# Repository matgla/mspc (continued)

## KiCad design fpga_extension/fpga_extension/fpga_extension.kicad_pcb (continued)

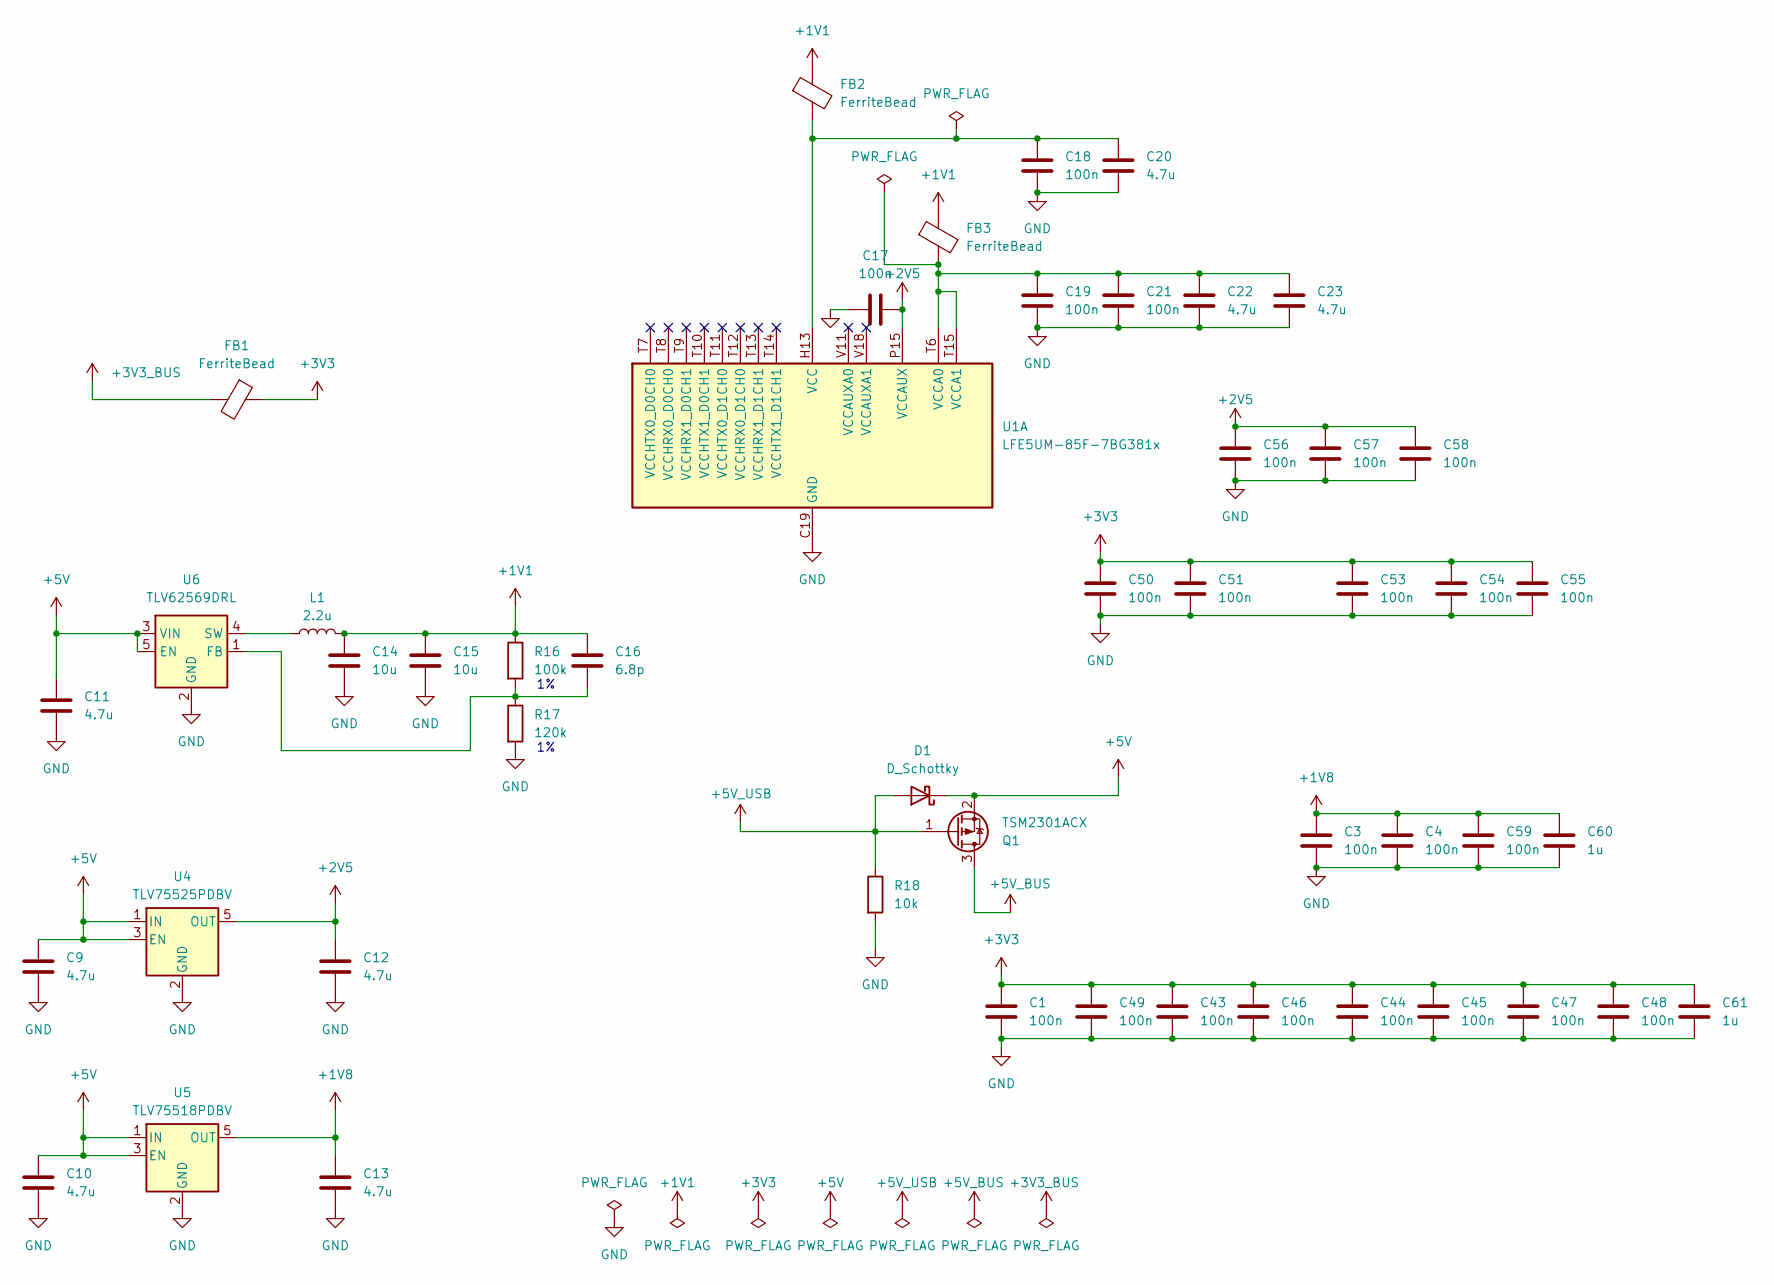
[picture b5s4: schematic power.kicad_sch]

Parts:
C1, C3, C4, C17, C18, C19, C21, C43, C44, C45, C46, C47, C48, C49, C50, C51, C53, C54, C55, C56, C57, C58, C59: 100n; C_0402_1005Metric_Pad0.74x0.62mm_HandSolder
C9, C10, C11, C12, C13, C20, C22, C23: 4.7u; C_0402_1005Metric_Pad0.74x0.62mm_HandSolder
C14, C15: 10u; C_0603_1608Metric_Pad1.08x0.95mm_HandSolder
C16: 6.8p; C_0402_1005Metric_Pad0.74x0.62mm_HandSolder
C60, C61: 1u; C_0402_1005Metric_Pad0.74x0.62mm_HandSolder
D1: D_Schottky; D_SOD-323_HandSoldering
FB1, FB2, FB3: FerriteBead; L_0805_2012Metric_Pad1.05x1.20mm_HandSolder
L1: 2.2u; L_0805_2012Metric_Pad1.15x1.40mm_HandSolder
Q1: TSM2301ACX; SOT-23W_Handsoldering
R16: 100k; R_0402_1005Metric_Pad0.72x0.64mm_HandSolder
R17: 120k; R_0402_1005Metric_Pad0.72x0.64mm_HandSolder
R18: 10k; R_0402_1005Metric_Pad0.72x0.64mm_HandSolder
U1: LFE5UM-85F-7BG381x; Lattice_caBGA-381_17.0x17.0mm_Layout20x20_P0.8mm_Ball0.4mm_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
U4: TLV75525PDBV; SOT-23-5
U5: TLV75518PDBV; SOT-23-5
U6: TLV62569DRL; SOT-563

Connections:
+1V1: C14.1, C15.1, C16.1, FB2.1, FB3.1, L1.2, R16.1
+1V8: C3.1, C4.1, C13.1, C59.1, C60.1, U5.5 (OUT); also elsewhere on the board
+2V5: C12.1, C17.2, C56.1, C57.1, C58.1, U1.F6 (VCCAUX), U1.F15 (VCCAUX), U1.P6 (VCCAUX), U1.P15 (VCCAUX), U4.5 (OUT)
+3V3: C1.1, C43.1, C44.1, C45.1, C46.1, C47.1, C48.1, C49.1, C50.1, C51.1, C53.1, C54.1, C55.1, C61.1, FB1.1; also elsewhere on the board
+3V3_BUS: FB1.2; also elsewhere on the board
+5V: C9.1, C10.1, C11.1, D1.1 (K), Q1.2 (S), U4.1 (IN), U4.3 (EN), U5.1 (IN), U5.3 (EN), U6.3 (VIN), U6.5 (EN)
+5V_BUS: Q1.3 (D); also elsewhere on the board
+5V_USB: D1.2 (A), Q1.1 (G), R18.1; also elsewhere on the board
GND: C1.2, C3.2, C4.2, C9.2, C10.2, C11.2, C12.2, C13.2, C14.2, C15.2, C17.1, C18.2, C19.2, C20.2, C21.2, C22.2, C23.2, C43.2, C44.2, C45.2, C46.2, C47.2, C48.2, C49.2, C50.2, C51.2, C53.2, C54.2, C55.2, C56.2, C57.2, C58.2, C59.2, C60.2, C61.2, R17.2, R18.2, U1.B7 (GND), U1.B14 (GND), U1.C19 (GND), U1.D4 (GND), U1.F7 (GND), U1.F8 (GND), U1.F13 (GND), U1.F14 (GND), U1.G4 (GND), U1.G6 (GND), U1.G7 (GND), U1.G8 (GND), U1.G9 (GND), U1.G10 (GND), U1.G11 (GND), U1.G12 (GND), U1.G13 (GND), U1.G14 (GND), U1.G15 (GND), U1.G17 (GND), U1.H19 (GND), U1.J2 (GND), U1.J7 (GND), U1.J9 (GND), U1.J10 (GND), U1.J11 (GND), U1.J12 (GND), U1.J14 (GND), U1.K6 (GND), U1.K7 (GND), U1.K9 (GND), U1.K10 (GND), U1.K11 (GND), U1.K12 (GND), U1.K14 (GND), U1.K15 (GND), U1.L9 (GND), U1.L10 (GND), U1.L11 (GND), U1.L12 (GND), U1.M2 (GND), U1.M7 (GND), U1.M9 (GND), U1.M10 (GND), U1.M11 (GND), U1.M12 (GND), U1.M14 (GND), U1.M16 (GND), U1.N6 (GND), U1.N7 (GND), U1.N14 (GND), U1.N15 (GND), U1.P7 (GND), U1.P8 (GND), U1.P11 (GND), U1.P12 (GND), U1.P13 (GND), U1.P14 (GND), U1.R19 (GND), U1.U7 (GND), U1.U8 (GND), U1.U9 (GND), U1.U10 (GND), U1.U11 (GND), U1.U12 (GND), U1.U13 (GND), U1.U14 (GND), U1.V5 (GND), U1.V6 (GND), U1.V7 (GND), U1.V8 (GND), U1.V9 (GND), U1.V12 (GND), U1.V13 (GND), U1.V14 (GND), U1.V15 (GND), U1.V16 (GND), U1.V19 (GND), U1.V20 (GND), U1.W6 (GND), U1.W7 (GND), U1.W12 (GND), U1.W15 (GND), U1.W16 (GND), U1.W19 (GND), U4.2 (GND), U5.2 (GND), U6.2 (GND); also elsewhere on the board
unnamed: C18.1, C20.1, FB2.2, U1.H8 (VCC), U1.H9 (VCC), U1.H10 (VCC), U1.H11 (VCC), U1.H12 (VCC), U1.H13 (VCC), U1.J8 (VCC), U1.J13 (VCC), U1.K8 (VCC), U1.K13 (VCC), U1.L8 (VCC), U1.L13 (VCC), U1.M8 (VCC), U1.M13 (VCC), U1.N8 (VCC), U1.N9 (VCC), U1.N10 (VCC), U1.N11 (VCC), U1.N12 (VCC), U1.N13 (VCC)
unnamed: C19.1, C21.1, C22.1, C23.1, FB3.2, U1.T6 (VCCA0), U1.T15 (VCCA1), U1.U6 (VCCA0), U1.U15 (VCCA1)
unnamed: C16.2, R16.2, R17.1, U6.1 (FB)
unnamed: L1.1, U6.4 (SW)

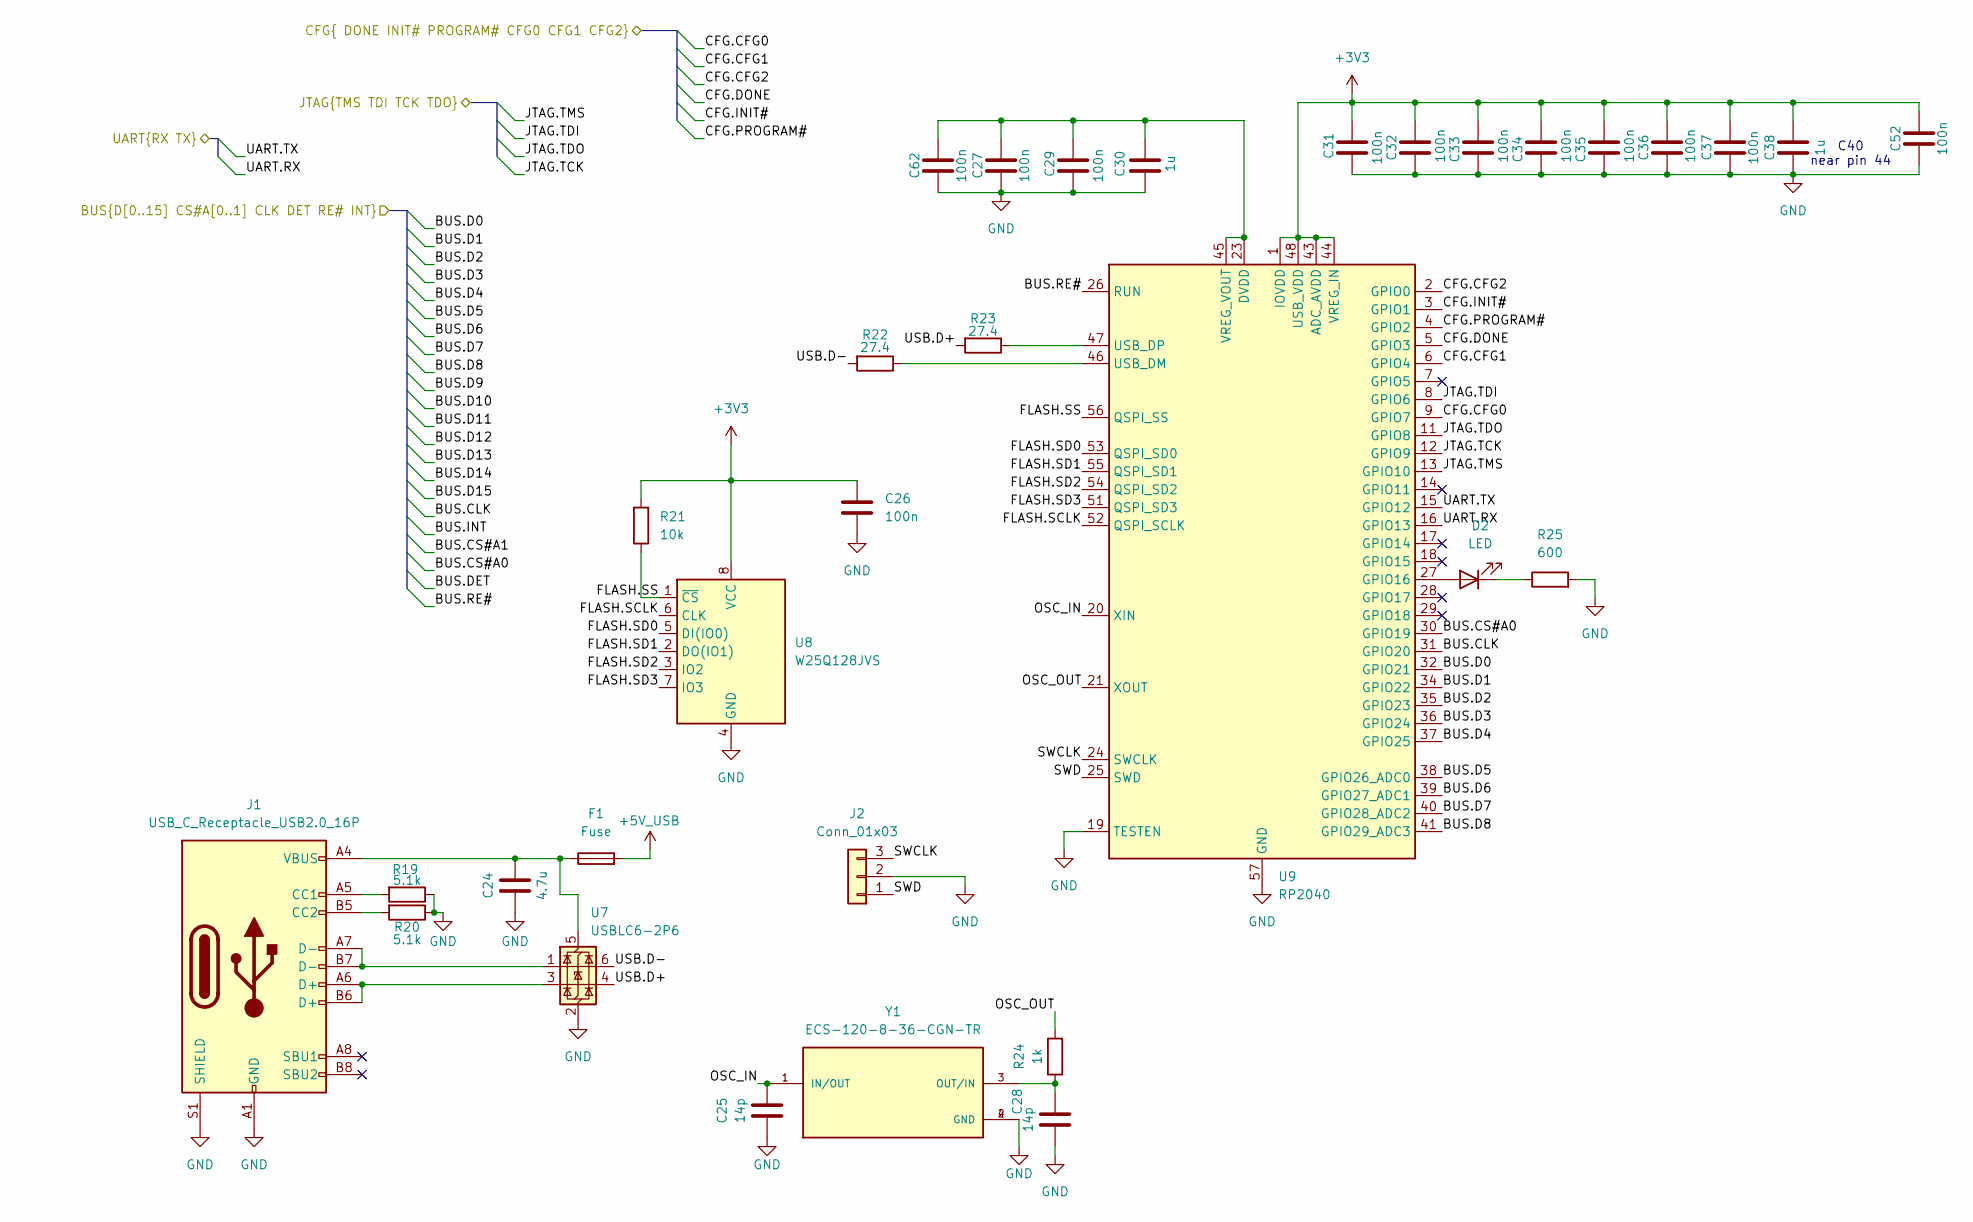
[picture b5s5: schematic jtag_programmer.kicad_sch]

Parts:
C24: 4.7u; C_0402_1005Metric_Pad0.74x0.62mm_HandSolder
C25, C28: 14p; C_0402_1005Metric_Pad0.74x0.62mm_HandSolder
C26, C27, C29, C31, C32, C33, C34, C35, C36, C37, C52, C62: 100n; C_0402_1005Metric_Pad0.74x0.62mm_HandSolder
C30, C38: 1u; C_0402_1005Metric_Pad0.74x0.62mm_HandSolder
D2: LED; LED_0402_1005Metric_Pad0.77x0.64mm_HandSolder
F1: Fuse; Fuse_0603_1608Metric_Pad1.05x0.95mm_HandSolder
J1: USB_C_Receptacle_USB2.0_16P; USB_C_Receptacle_HRO_TYPE-C-31-M-12
J2: Conn_01x03; PinHeader_1x03_P2.54mm_Vertical
R19, R20: 5.1k; R_0402_1005Metric_Pad0.72x0.64mm_HandSolder
R21: 10k; R_0402_1005Metric_Pad0.72x0.64mm_HandSolder
R22, R23: 27.4; R_0402_1005Metric_Pad0.72x0.64mm_HandSolder
R24: 1k; R_0402_1005Metric_Pad0.72x0.64mm_HandSolder
R25: 600; R_0402_1005Metric_Pad0.72x0.64mm_HandSolder
U7: USBLC6-2P6; SOT-666
U8: W25Q128JVS; SOIC-8_5.23x5.23mm_P1.27mm
U9: RP2040; QFN-56-1EP_7x7mm_P0.4mm_EP3.2x3.2mm
Y1: ECS-120-8-36-CGN-TR; XTAL_ECS-120-8-36-CGN-TR; PARTREV 2017

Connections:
+3V3: C26.1, C31.1, C32.1, C33.1, C34.1, C35.1, C36.1, C37.1, C38.1, C52.1, R21.2, U8.8 (VCC), U9.1 (IOVDD), U9.10 (IOVDD), U9.22 (IOVDD), U9.33 (IOVDD), U9.42 (IOVDD), U9.43 (ADC_AVDD), U9.44 (VREG_IN), U9.48 (USB_VDD), U9.49 (IOVDD); also elsewhere on the board
+5V_USB: F1.2; also elsewhere on the board
/Connector/BUS.CLK: U9.31 (GPIO20); also elsewhere on the board
/Connector/BUS.CS#A0: U9.30 (GPIO19); also elsewhere on the board
/Connector/BUS.D0: U9.32 (GPIO21); also elsewhere on the board
/Connector/BUS.D1: U9.34 (GPIO22); also elsewhere on the board
/Connector/BUS.D2: U9.35 (GPIO23); also elsewhere on the board
/Connector/BUS.D3: U9.36 (GPIO24); also elsewhere on the board
/Connector/BUS.D4: U9.37 (GPIO25); also elsewhere on the board
/Connector/BUS.D5: U9.38 (GPIO26_ADC0); also elsewhere on the board
/Connector/BUS.D6: U9.39 (GPIO27_ADC1); also elsewhere on the board
/Connector/BUS.D7: U9.40 (GPIO28_ADC2); also elsewhere on the board
/Connector/BUS.D8: U9.41 (GPIO29_ADC3); also elsewhere on the board
/Connector/BUS.RE#: U9.26 (RUN); also elsewhere on the board
/FPGA Configuration/CFG.CFG0: U9.9 (GPIO7); also elsewhere on the board
/FPGA Configuration/CFG.CFG1: U9.6 (GPIO4); also elsewhere on the board
/FPGA Configuration/CFG.CFG2: U9.2 (GPIO0); also elsewhere on the board
/FPGA Configuration/CFG.DONE: U9.5 (GPIO3); also elsewhere on the board
/FPGA Configuration/CFG.INIT#: U9.3 (GPIO1); also elsewhere on the board
/FPGA Configuration/CFG.PROGRAM#: U9.4 (GPIO2); also elsewhere on the board
/FPGA Configuration/JTAG.TCK: U9.12 (GPIO9); also elsewhere on the board
/FPGA Configuration/JTAG.TDI: U9.8 (GPIO6); also elsewhere on the board
/FPGA Configuration/JTAG.TDO: U9.11 (GPIO8); also elsewhere on the board
/FPGA Configuration/JTAG.TMS: U9.13 (GPIO10); also elsewhere on the board
/JTAG/FLASH.SCLK: U8.6 (CLK), U9.52 (QSPI_SCLK)
/JTAG/FLASH.SD0: U8.5 (DI(IO0)), U9.53 (QSPI_SD0)
/JTAG/FLASH.SD1: U8.2 (DO(IO1)), U9.55 (QSPI_SD1)
/JTAG/FLASH.SD2: U8.3 (IO2), U9.54 (QSPI_SD2)
/JTAG/FLASH.SD3: U8.7 (IO3), U9.51 (QSPI_SD3)
/JTAG/FLASH.SS: R21.1, U8.1 (~CS), U9.56 (QSPI_SS)
/JTAG/OSC_IN: C25.1, U9.20 (XIN), Y1.1 (IN/OUT)
/JTAG/OSC_OUT: R24.2, U9.21 (XOUT)
/JTAG/SWCLK: J2.3, U9.24 (SWCLK)
/JTAG/SWD: J2.1, U9.25 (SWD)
/JTAG/UART.RX: U9.16 (GPIO13); also elsewhere on the board
/JTAG/UART.TX: U9.15 (GPIO12); also elsewhere on the board
/JTAG/USB.D+: R23.2, U7.4 (I/O2)
/JTAG/USB.D-: R22.2, U7.6 (I/O1)
GND: C24.1, C25.2, C26.2, C27.2, C28.2, C29.2, C30.2, C31.2, C32.2, C33.2, C34.2, C35.2, C36.2, C37.2, C38.2, C52.2, C62.2, J1.A1 (GND), J1.A12 (GND), J1.B1 (GND), J1.B12 (GND), J1.S1 (SHIELD), J2.2, R19.1, R20.1, R25.2, U7.2 (GND), U8.4 (GND), U9.19 (TESTEN), U9.57 (GND), Y1.2 (GND), Y1.4 (GND); also elsewhere on the board
unnamed: D2.2 (A), U9.27 (GPIO16)
unnamed: D2.1 (K), R25.1
unnamed: J1.A5 (CC1), R19.2
unnamed: J1.B5 (CC2), R20.2
unnamed: J1.A6 (D+), J1.B6 (D+), U7.3 (I/O2)
unnamed: J1.A7 (D-), J1.B7 (D-), U7.1 (I/O1)
unnamed: C24.2, F1.1, J1.A4 (VBUS), J1.A9 (VBUS), J1.B4 (VBUS), J1.B9 (VBUS), U7.5 (VBUS)
unnamed: R22.1, U9.46 (USB_DM)
unnamed: R23.1, U9.47 (USB_DP)
unnamed: C27.1, C29.1, C30.1, C62.1, U9.23 (DVDD), U9.45 (VREG_VOUT), U9.50 (DVDD)
unnamed: C28.1, R24.1, Y1.3 (OUT/IN)

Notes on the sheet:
C40 near pin 44

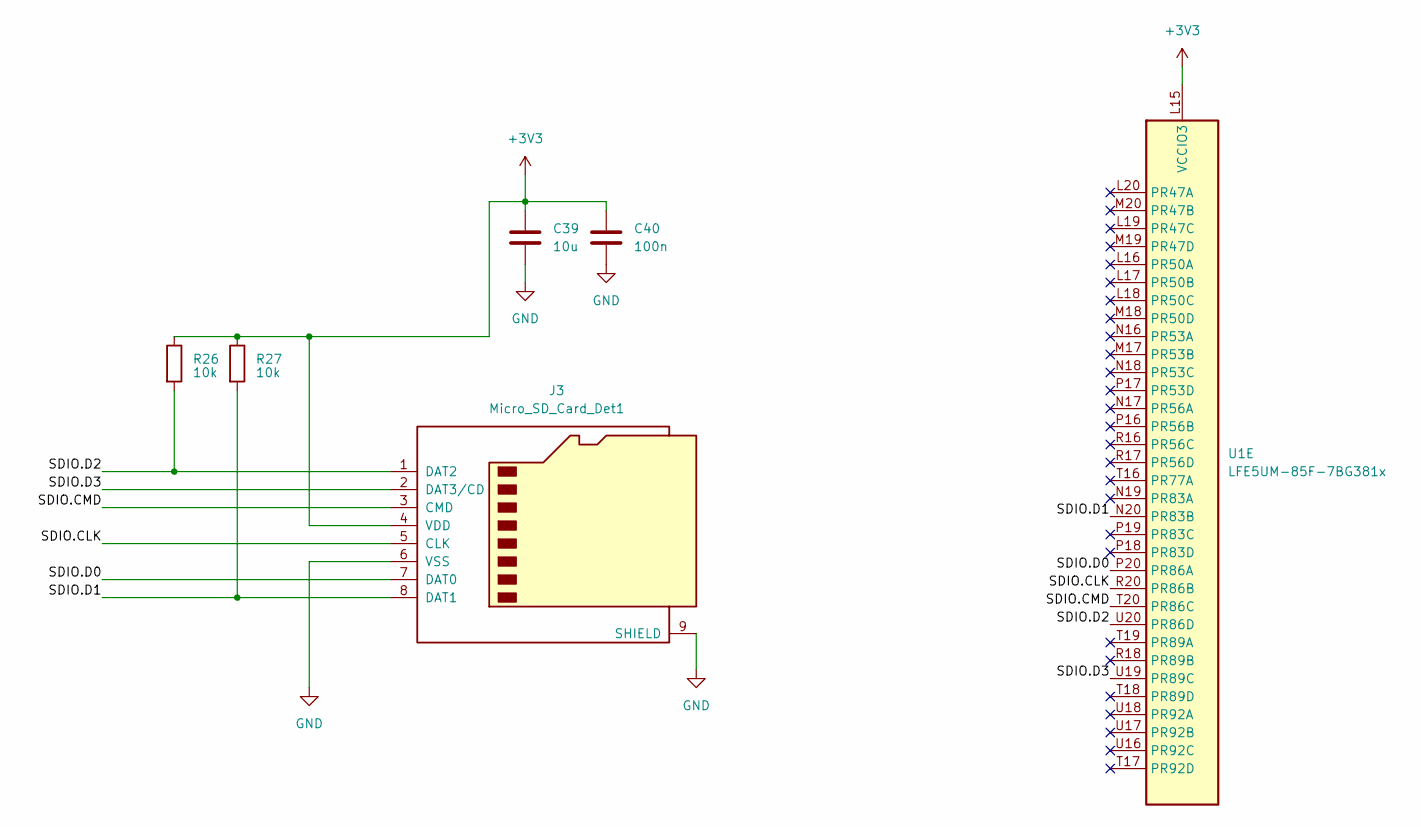
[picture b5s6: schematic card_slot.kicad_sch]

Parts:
C39: 10u; C_0402_1005Metric_Pad0.74x0.62mm_HandSolder
C40: 100n; C_0402_1005Metric_Pad0.74x0.62mm_HandSolder
J3: Micro_SD_Card_Det1; microSD_HC_Wuerth_693072010801
R26, R27: 10k; R_0402_1005Metric_Pad0.72x0.64mm_HandSolder
U1: LFE5UM-85F-7BG381x; Lattice_caBGA-381_17.0x17.0mm_Layout20x20_P0.8mm_Ball0.4mm_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

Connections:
+3V3: C39.1, C40.1, J3.4 (VDD), R26.1, R27.1, U1.L14 (VCCIO3), U1.L15 (VCCIO3), U1.M15 (VCCIO3); also elsewhere on the board
/SD/SDIO.CLK: J3.5 (CLK), U1.R20 (PR86B)
/SD/SDIO.CMD: J3.3 (CMD), U1.T20 (PR86C)
/SD/SDIO.D0: J3.7 (DAT0), U1.P20 (PR86A)
/SD/SDIO.D1: J3.8 (DAT1), R27.2, U1.N20 (PR83B)
/SD/SDIO.D2: J3.1 (DAT2), R26.2, U1.U20 (PR86D)
/SD/SDIO.D3: J3.2 (DAT3/CD), U1.U19 (PR89C)
GND: C39.2, C40.2, J3.6 (VSS), J3.9 (SHIELD); also elsewhere on the board

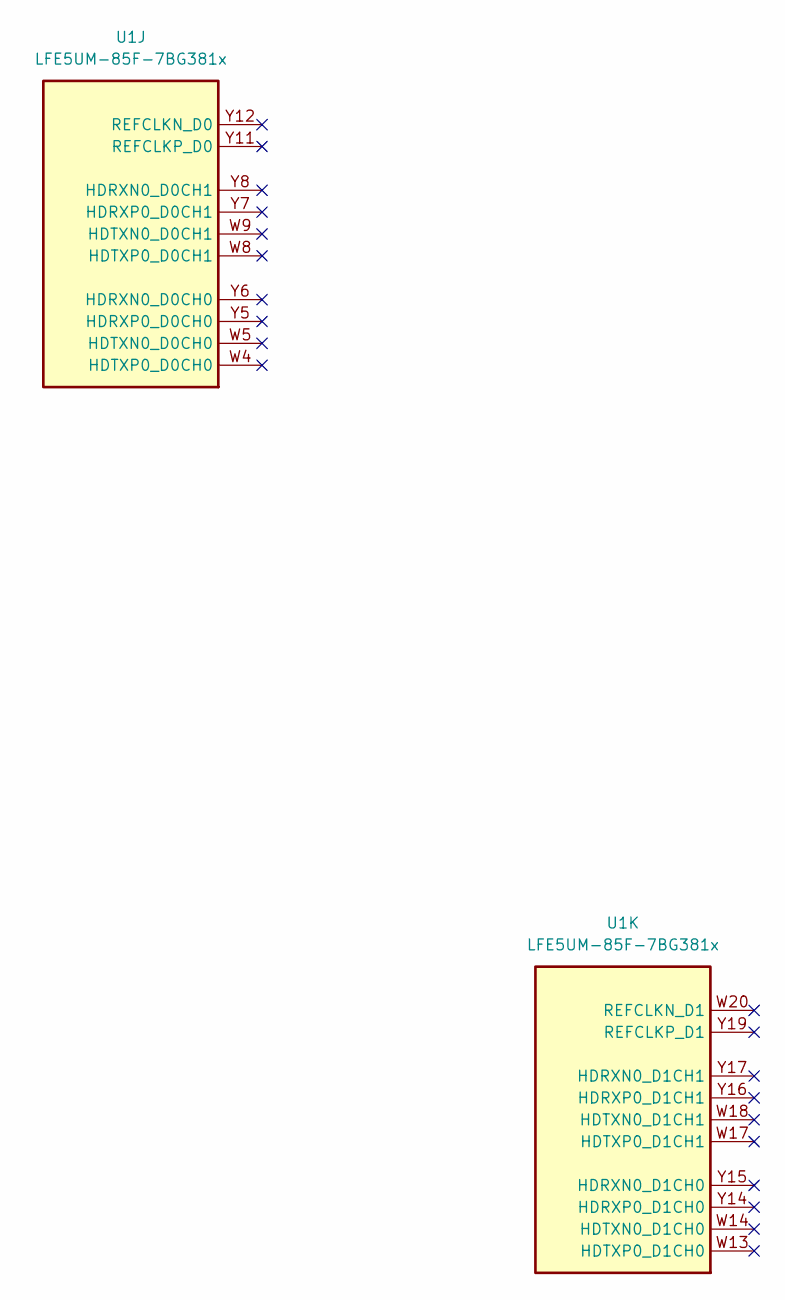
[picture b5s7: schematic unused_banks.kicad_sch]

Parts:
U1: LFE5UM-85F-7BG381x; Lattice_caBGA-381_17.0x17.0mm_Layout20x20_P0.8mm_Ball0.4mm_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

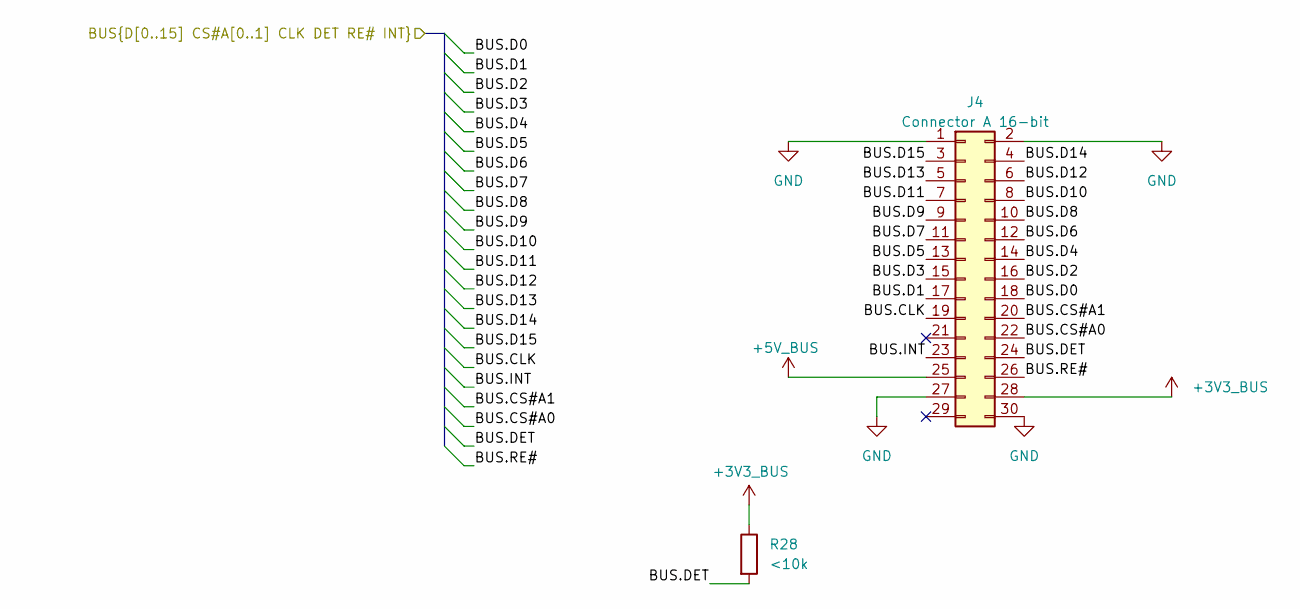
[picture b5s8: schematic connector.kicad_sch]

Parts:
J4: Connector A 16-bit; PinHeader_2x15_P1.27mm_Vertical_SMD
R28: <10k; R_0402_1005Metric_Pad0.72x0.64mm_HandSolder

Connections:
+3V3_BUS: J4.28, R28.1; also elsewhere on the board
+5V_BUS: J4.25; also elsewhere on the board
/Connector/BUS.CLK: J4.19; also elsewhere on the board
/Connector/BUS.CS#A0: J4.22; also elsewhere on the board
/Connector/BUS.CS#A1: J4.20; also elsewhere on the board
/Connector/BUS.D0: J4.18; also elsewhere on the board
/Connector/BUS.D1: J4.17; also elsewhere on the board
/Connector/BUS.D2: J4.16; also elsewhere on the board
/Connector/BUS.D3: J4.15; also elsewhere on the board
/Connector/BUS.D4: J4.14; also elsewhere on the board
/Connector/BUS.D5: J4.13; also elsewhere on the board
/Connector/BUS.D6: J4.12; also elsewhere on the board
/Connector/BUS.D7: J4.11; also elsewhere on the board
/Connector/BUS.D8: J4.10; also elsewhere on the board
/Connector/BUS.D9: J4.9; also elsewhere on the board
/Connector/BUS.D10: J4.8; also elsewhere on the board
/Connector/BUS.D11: J4.7; also elsewhere on the board
/Connector/BUS.D12: J4.6; also elsewhere on the board
/Connector/BUS.D13: J4.5; also elsewhere on the board
/Connector/BUS.D14: J4.4; also elsewhere on the board
/Connector/BUS.D15: J4.3; also elsewhere on the board
/Connector/BUS.DET: J4.24, R28.2
/Connector/BUS.INT: J4.23; also elsewhere on the board
/Connector/BUS.RE#: J4.26; also elsewhere on the board
GND: J4.1, J4.2, J4.27, J4.30; also elsewhere on the board

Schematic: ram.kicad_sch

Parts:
C5, C7: 100n; C_0402_1005Metric_Pad0.74x0.62mm_HandSolder
C6, C8: 4.7u; C_0402_1005Metric_Pad0.74x0.62mm_HandSolder
U1: LFE5UM-85F-7BG381x; Lattice_caBGA-381_17.0x17.0mm_Layout20x20_P0.8mm_Ball0.4mm_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
U3: W958D8NBYA; BGA24C100P5X5_600X800X120

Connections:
+1V8: C5.1, C6.1, C7.1, C8.1, U1.H6 (VCCIO7), U1.H7 (VCCIO7), U1.J6 (VCCIO7), U3.B4 (VCC), U3.D1 (VCCQ), U3.E4 (VCCQ); also elsewhere on the board
/RAM/HYPERRAM.CK+: U1.A4 (PL11A), U3.B2 (CK)
/RAM/HYPERRAM.CK-: U1.A5 (PL11B), U3.B1 (CK#)
/RAM/HYPERRAM.CS#: U1.A3 (PL14C), U3.A3 (CS#)
/RAM/HYPERRAM.DQ0: U1.D1 (PL38B), U3.D3 (DQ0)
/RAM/HYPERRAM.DQ1: U1.B2 (PL35C), U3.D2 (DQ1)
/RAM/HYPERRAM.DQ2: U1.B1 (PL35B), U3.C4 (DQ2)
/RAM/HYPERRAM.DQ3: U1.C2 (PL35D), U3.D4 (DQ3)
/RAM/HYPERRAM.DQ4: U1.C1 (PL38A), U3.D5 (DQ4)
/RAM/HYPERRAM.DQ5: U1.D2 (PL38C), U3.E3 (DQ5)
/RAM/HYPERRAM.DQ6: U1.E1 (PL38D), U3.E2 (DQ6)
/RAM/HYPERRAM.DQ7: U1.D3 (PL17D), U3.E1 (DQ7)
/RAM/HYPERRAM.RESET#: U1.A2 (PL35A), U3.A4 (RESET#)
/RAM/HYPERRAM.RWDS: U1.B3 (PL14D), U3.C3 (RWDS)
GND: C5.2, C6.2, C7.2, C8.2, U3.B3 (VSS), U3.C1 (VSSQ), U3.E5 (VSSQ); also elsewhere on the board

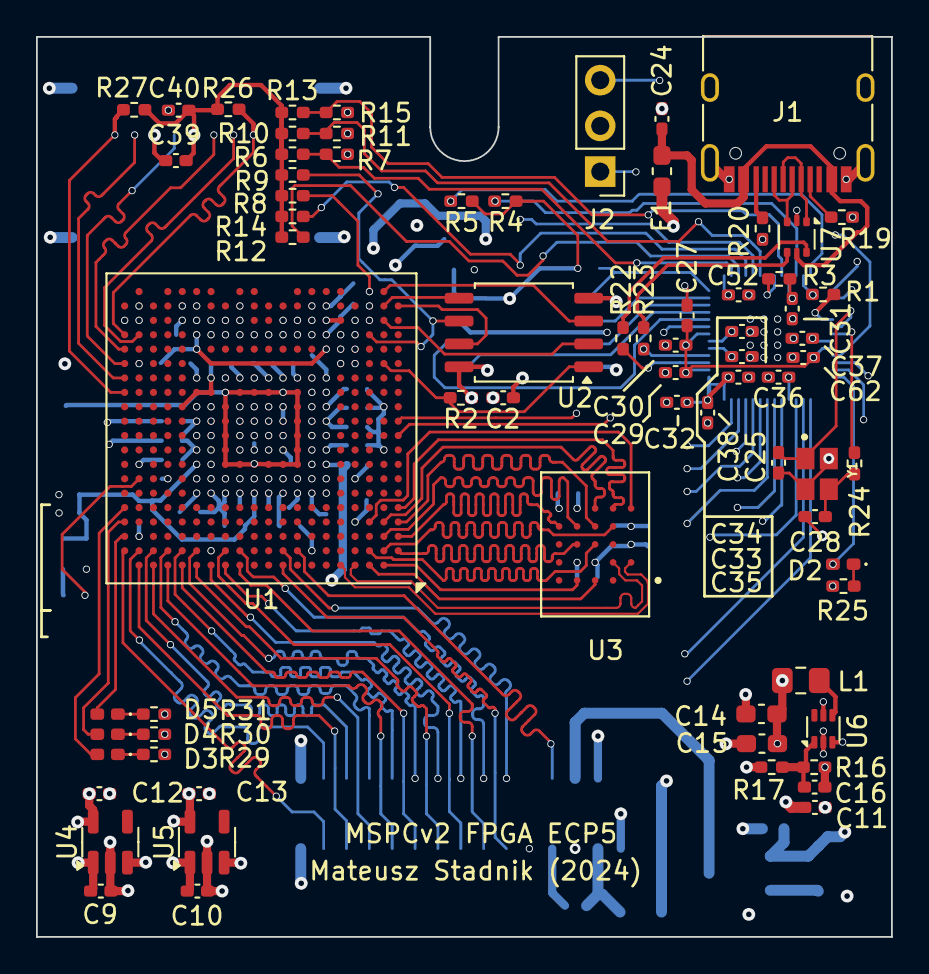
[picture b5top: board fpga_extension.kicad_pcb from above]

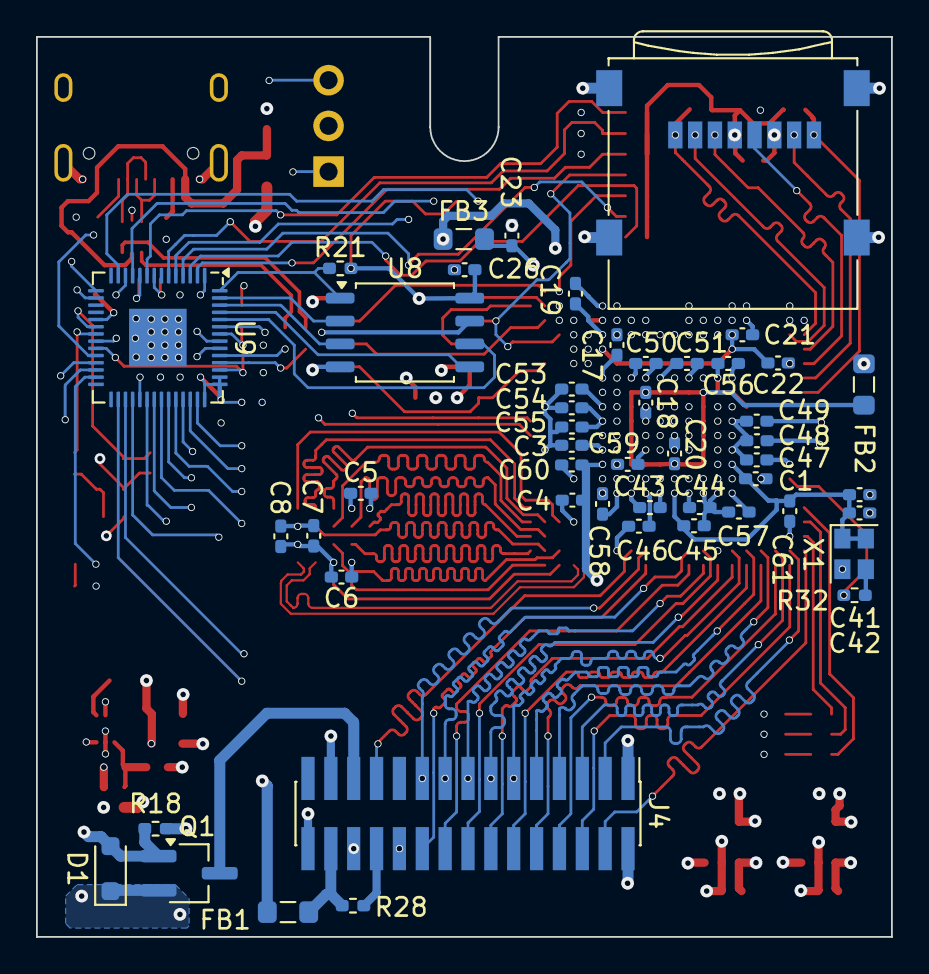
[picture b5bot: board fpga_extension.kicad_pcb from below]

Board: 6 copper layers, 47.5 x 50.0 mm, 120 parts (49 on the bottom side), 103 nets.

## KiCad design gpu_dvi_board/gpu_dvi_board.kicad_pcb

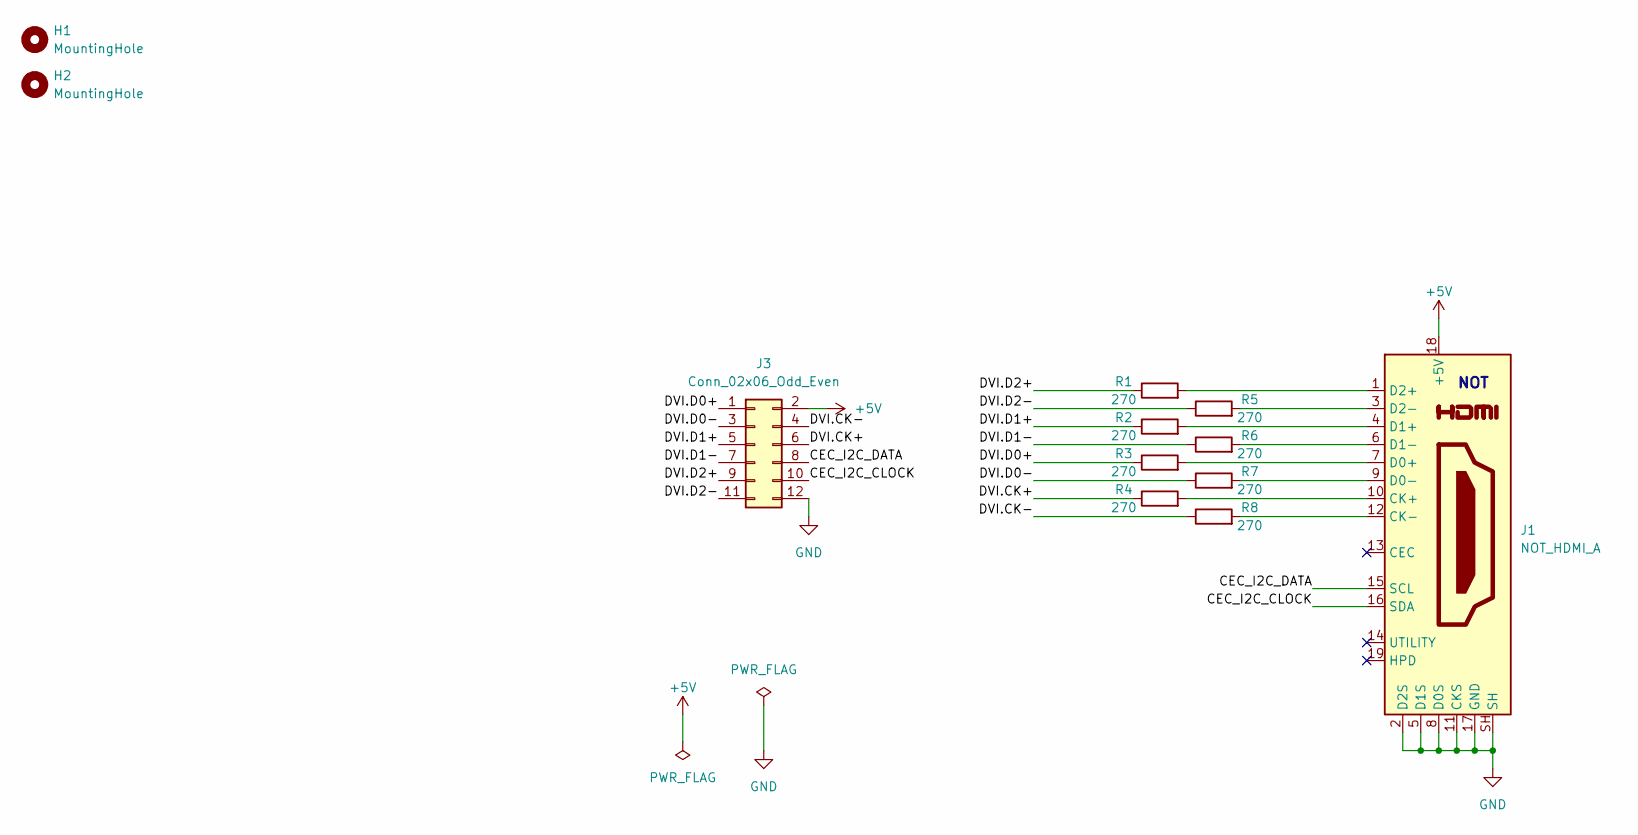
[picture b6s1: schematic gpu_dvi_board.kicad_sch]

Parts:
H1, H2: MountingHole; MountingHole_2.2mm_M2
J1: NOT_HDMI_A; HDMI_A_Molex_208658-1001_Horizontal
J3: Conn_02x06_Odd_Even; PinHeader_2x06_P1.27mm_Vertical_SMD
R1, R2, R3, R4, R5, R6, R7, R8: 270; R_0402_1005Metric_Pad0.72x0.64mm_HandSolder

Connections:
+5V: J1.18 (+5V), J3.2
/CEC_I2C_CLOCK: J1.16 (SDA), J3.10
/CEC_I2C_DATA: J1.15 (SCL), J3.8
/DVI.CK+: J3.6, R4.1
/DVI.CK-: J3.4, R8.1
/DVI.D0+: J3.1, R3.1
/DVI.D0-: J3.3, R7.1
/DVI.D1+: J3.5, R2.1
/DVI.D1-: J3.7, R6.1
/DVI.D2+: J3.9, R1.1
/DVI.D2-: J3.11, R5.1
GND: J1.2 (D2S), J1.5 (D1S), J1.8 (D0S), J1.11 (CKS), J1.17 (GND), J1.SH, J3.12
unnamed: J1.10 (CK+), R4.2
unnamed: J1.12 (CK-), R8.2
unnamed: J1.7 (D0+), R3.2
unnamed: J1.9 (D0-), R7.2
unnamed: J1.4 (D1+), R2.2
unnamed: J1.6 (D1-), R6.2
unnamed: J1.1 (D2+), R1.2
unnamed: J1.3 (D2-), R5.2

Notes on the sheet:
NOT

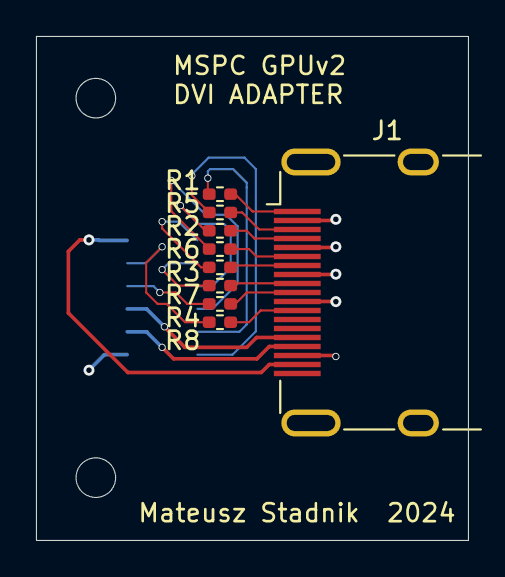
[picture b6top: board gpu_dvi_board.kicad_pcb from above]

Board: 4 copper layers, 24.0 x 28.0 mm, 12 parts (1 on the bottom side), 20 nets.

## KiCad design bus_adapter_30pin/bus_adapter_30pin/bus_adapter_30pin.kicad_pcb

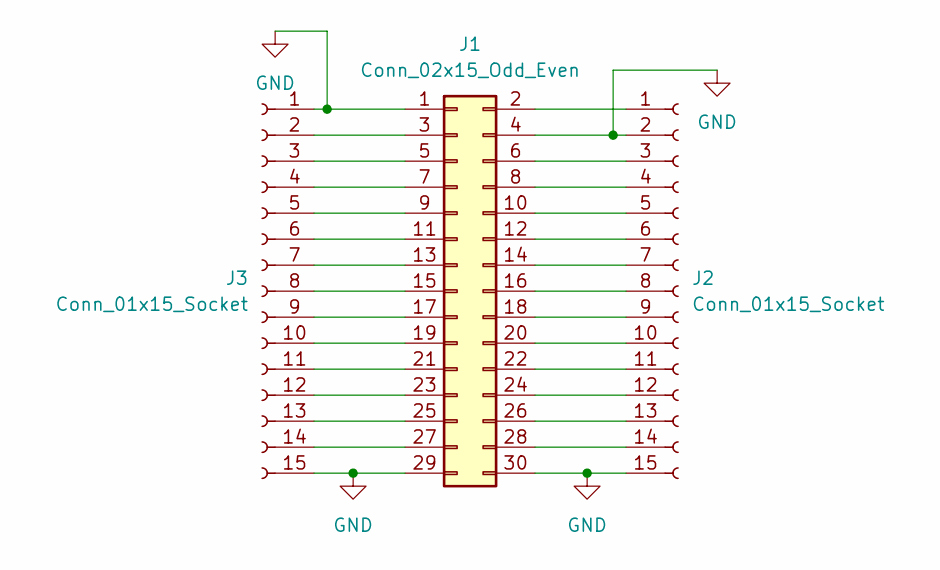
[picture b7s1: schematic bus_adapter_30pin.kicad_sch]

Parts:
J1: Conn_02x15_Odd_Even; PinHeader_2x15_P1.27mm_Vertical_SMD
J2, J3: Conn_01x15_Socket; PinHeader_1x15_P2.54mm_Vertical

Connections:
GND: J1.1, J1.4, J1.29, J1.30, J2.2, J2.15, J3.1, J3.15
unnamed: J1.2, J2.1
unnamed: J1.3, J3.2
unnamed: J1.5, J3.3
unnamed: J1.6, J2.3
unnamed: J1.7, J3.4
unnamed: J1.8, J2.4
unnamed: J1.9, J3.5
unnamed: J1.10, J2.5
unnamed: J1.11, J3.6
unnamed: J1.12, J2.6
unnamed: J1.13, J3.7
unnamed: J1.14, J2.7
unnamed: J1.15, J3.8
unnamed: J1.16, J2.8
unnamed: J1.17, J3.9
unnamed: J1.18, J2.9
unnamed: J1.19, J3.10
unnamed: J1.20, J2.10
unnamed: J1.21, J3.11
unnamed: J1.22, J2.11
unnamed: J1.23, J3.12
unnamed: J1.24, J2.12
unnamed: J1.25, J3.13
unnamed: J1.26, J2.13
unnamed: J1.27, J3.14
unnamed: J1.28, J2.14

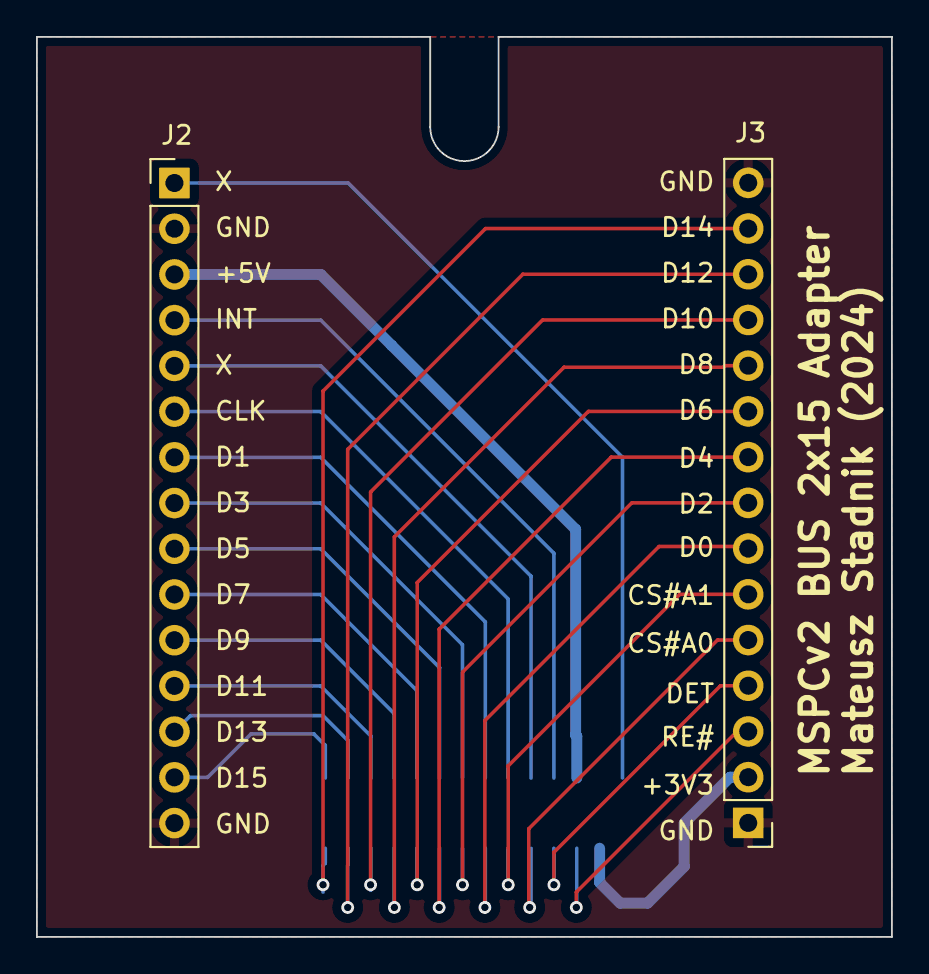
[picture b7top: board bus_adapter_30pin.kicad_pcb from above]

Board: 2 copper layers, 47.5 x 50.0 mm, 3 parts (1 on the bottom side), 27 nets.
